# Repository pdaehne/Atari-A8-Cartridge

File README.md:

# Atari A8 Cartridge

This repository contains the KiCad project and Gerber files for a simple
cartridge for the Atari 8-Bit Computers (Atari 400/800/XL/XE/XEGS). It supports
8 KiB and 16 KiB cartridge images that do not need memory mappers. You may put
multiple cartridge images on one cartridge, and select which one of the images
to start by using DIP switches, pin headers and jumpers.

## Ordering the PCB

The subdirectory "gerber-files" contains a Zip file you can use to order the PCB
from PCB manufacturers like PCBWay or JLCPCB. Simply upload the Zip on their web
page. Order the standard PCB thickness of 1.6mm. I also recommend to order a
surface finish of ENIG with gold fingers and chamfered edges, because it is much
more durable than the default HASL finish.

## Building the Cartridge

### Bill of Materials

* __1x 27(C)512 / 27(C)256 / 27(C)128 / 27(C)64 EPROM__.

  This is where you store your cartridge images. 27(C)512 have a capacity of 64
  KiB, 27(C)256 have 32 KiB, 27(C)128 have 16 KiB, and 27(C)64 have 8 KiB.

* (Optional) __1x 28 Pin Socket 2.54mm pitch 15.42mm width__.

  This is the socket for the EPROM. It is optional, you can also solder the
  EPROM directly to the PCB, but I prefer to use sockets. Keep in mind that the
  cartridge will not fit into a cartridge shell when you use sockets.

* __1x Ceramic Capacitor 100nF 2.5mm pitch__.

  This is the blocking capacitor for the EPROM.

* (Optional) __4x 10 kOhm Resistors DIN 0207__.

  These are pull-up resistors. Three of them are used on the DIP switches for
  the address lines A13, A14 and A15. When you do not plan to use the DIP
  switches, you can leave them away. The last one of the resistors is used to
  create the Chip Select (<span style="text-decoration:overline">CS</span>)
  signal for the EPROM when using 16 KiB ROMs. When you do not plan to use 16
  KiB ROMs, you can leave that resistor away.

* (Optional) __2x Diodes 1N4148 DO-35__.

  These are switching diodes used to create the Chip Select
  (<span style="text-decoration:overline">CS</span>) signal for the EPROM when
  using 16 KiB ROMs. When you do not plan to use 16 KiB ROMs, you can leave
  these diodes away.

* (Optional) __1x 1x3 Pin Header 2.54mm pitch__.

  Used to switch between 8 KiB and 16 KiB ROMs. When you do not need to switch
  between 8 KiB and 16 KiB ROMs, you can leave this pin header away and select
  a static configuration with a solder jumper.

* (Optional) __1x 2x3 Pin Header 2.54mm pitch__.

  Used to select the signal that goes to the Chip Select
  (<span style="text-decoration:overline">CS</span>) pin of the EPROM. This pin
  header is optional, you can select a static configuration with a solder
  jumper.

* (Optional) __2x Jumpers 2.54mm pitch__.

  Used on the pin headers to select the signal that goes to the Chip Select
  (<span style="text-decoration:overline">CS</span>) pin of the EPROM as well
  as to switch between 8 KiB and 16 KiB ROMs.

### Soldering the Pull-up Resistors on the Address Lines

We start with soldering the three pull-up resistors on the DIP switches that
control the address lines A13, A14 and A15. These are optional - when you do not
plan to use the DIP switches, you can leave these three resistors away.

### Soldering the Pull-up Resistor and Diodes for the 16 KiB Chip Select Signal

Then, we solder the single pull-up resistor and the two diodes that generate the
Chip Select (<span style="text-decoration:overline">CS</span>) signal for 16 KiB
ROMs. These are also optional - when you do not plan to use 16 KiB ROMs, you can
leave the resistor and the diodes away.

### Soldering the EPROM Socket

Now we solder the EPROM socket. This socket is optional, you can also solder the
EPROM directly to the cartridge, but I prefer sockets. Keep in mind that the
EPROM in a socket does not fit any cartridge case!

When soldering the EPROM directly to the cartridge, of course you have to fill
it with data before doing so!

Make sure that the notch of the socket points into the direction marked on the
silk screen of the PCB (up in the image below).

### Soldering the Capacitor

Next, solder the blocking capacitor to the cartridge.

### Soldering the Pin Header for the Chip Select Signal

Next, we solder the pin header used to configure the Chip Select
(<span style="text-decoration:overline">CS</span>) signal. More in detail
information about the configuration of the cartridge using these pin headers is
available in the section [Using the Cartridge](#using-the-cartridge) below.

Using the pin headers is optional, you can also generate a static configuration
by using corresponding solder jumpers on the back of the cartridge. Keep in mind
that you will not be able to put the cartridge into a case when you use the pin
headers!

### Soldering the DIP Switch

Now, we solder the DIP switch used to configure the RD4 and RD5 signals of the
cartridge as well as the address lines A13, A14 and A15 of the EPROM. You should
orient the DIP switch so that the "on" position of the sliders is to the right
of the cartridge as shown in the image below.

Using the DIP switch is optional, you can also generate a static configuration
by using corresponding solder jumpers on the back of the cartridge. Keep in mind
that you will not be able to put the cartridge into a case when you use the DIP
switch.

### Soldering the Pin Header for Selecting 8 KiB or 16 KiB Cartridge ROMs 

Next, we solder the pin header used to configure the cartridge for 8 KiB or 16
KiB ROMs.

Using the pin headers is optional, you can also generate a static configuration
by using corresponding solder jumpers on the back of the cartridge. Keep in mind
that you will not be able to put the cartridge into a case when you use the pin
headers!

### 3D-Printing a Case

In the subdirectory "[case](case)" of this repository there are STL files you can use to
print a case for the cartridge on your 3D printer. I even managed to fit an
EPROM with its socket into this case, but your mileage may vary, depending on
the length of the EPROM legs. You need two self-tapping flat-headed M3 Phillips
screws. Mine had a length of 12mm, but any length between 10mm and 17mm should
work.

There are two variants of the top part of the case, one with holes you can use
to access the DIP switches and the pin headers, and one closed version in case
your cartridge uses a fixed configuration.

### Using the Cartridge

This section explains how to use the cartridge, i.e. how to burn one or more
cartridge images onto the EPROM, and how to configure the cartridge to start one
of the images. There are DIP switches and two pin headers on the cartridge for
configuration. Two of the DIP switches configure the RD4 and RD5 signal lines of
the cartridge, i.e. they tell the computer where in the address space the
cartridge should show up. The remaining DIP switches configure the address lines
A13, A14, and A15, i.e. they determine the location of the ROM file on the
EPROM. One of the pin headers configures the Chip Select
(<span style="text-decoration:overline">CS</span>) signal of the EPROM, and the
other pin header configures the cartridge for 8 KiB or 16 KiB ROMs. When you do
not need the flexibility of configuring the cartridge using DIP switches or pin
headers and jumpers, there are corresponding solder jumpers on the back of the
cartridge that you can use to create a fixed configuration using solder blobs.

You do not need to worry if your configuration is correct, neither the cartridge
nor you Atari computer can be damaged by a wrong configuration, it simply will
not work.

> [!WARNING]
> Never change the configuration while the Atari computer is running. Always
> switch off the computer before changing the configuration or plugging in or
> removing the cartridge from the computer, otherwise you may damage the
> cartridge or your computer.

There are three types of ROMs supported by this cartridge:

  1. 8 KiB ROMs that get mapped at address range 32768-40959 ($8000-$9fff). This
     type of ROM is almost never used.
  2. 8 KiB ROMs that get mapped at address range 40960-49151 ($a000-$bfff).
  3. 16 KiB ROMs that get mapped at address range 32768-49151 ($8000-$bfff).

The following table show the settings used to configure the cartridge for these
three types of ROMs (and a fourth configuration which disables the cartridge).
You have to set the RD4 and RD5 DIP switches, connect the top, middle or bottom
two pins of the 2x3 pin header for the Chip Select signal, and you have to
connect either the left two or the right two pins of the 3x1 pin header for the
8 KiB / 16 KiB ROM size:

| RD4 / RD5 | Chip Select | ROM Size | Meaning |
|-----------|-------------|----------| --------|
| <picture><source media="(prefers-color-scheme: dark)" srcset="images/rd4_off_rd5_off.dark.svg"></picture> | Does not matter | Does not matter | Cartridge is disabled |
| <picture><source media="(prefers-color-scheme: dark)" srcset="images/rd4_on_rd5_off.dark.svg"></picture> | <picture><source media="(prefers-color-scheme: dark)" srcset="images/CS_S4.dark.svg"></picture> | <picture><source media="(prefers-color-scheme: dark)" srcset="images/8k.dark.svg"></picture> | 8 KiB cartridge at address range 32768-40959 ($8000-$9fff) |
| <picture><source media="(prefers-color-scheme: dark)" srcset="images/rd4_off_rd5_on.dark.svg"></picture> | <picture><source media="(prefers-color-scheme: dark)" srcset="images/CS_S5.dark.svg"></picture> | <picture><source media="(prefers-color-scheme: dark)" srcset="images/8k.dark.svg"></picture> | 8 KiB cartridge at address range 40960-49151 ($a000-$bfff) |
| <picture><source media="(prefers-color-scheme: dark)" srcset="images/rd4_on_rd5_on.dark.svg"></picture> | <picture><source media="(prefers-color-scheme: dark)" srcset="images/CS_S4_S5.dark.svg"></picture> | <picture><source media="(prefers-color-scheme: dark)" srcset="images/16k.dark.svg"></picture> | 16 KiB cartridge at address range 32768-49151 ($8000-$bfff) |

All other configurations not shown in the above table are invalid!

The remaining three DIP switches for the address lines A13, A14 and A15
determine the location of the ROM on the EPROM. Moving a DIP switch to the right
sets the corresponding address line to logic "0", and moving the switch to the
left sets the address line to "1". The cartridge supports 27(C)512, 27(C)256,
27(C)128, and 27(C)64 EPROMs which have different capacities and can store
different numbers of ROMs.

On 27(C)512 EPROMs with 64 KiB capacity, there are 8 slots where you may put ROM
images. 8 KiB ROMs require one single slot and may start at any of these slots,
16 KiB ROMs require two slots and must start at slots 1, 3, 5 or 7. You can
arbitrarily mix different image sizes to fill the available space. The following
table shows all possible combinations:

| Address Lines | Meaning |
|---------------|---------|
| <picture><source media="(prefers-color-scheme: dark)" srcset="images/slot1.dark.svg"></picture> | Slot 1 at address range 0-8191 ($0-$1fff) |
| <picture><source media="(prefers-color-scheme: dark)" srcset="images/slot2.dark.svg"></picture> | Slot 2 at address range 8192-16383 ($2000-$3fff) |
| <picture><source media="(prefers-color-scheme: dark)" srcset="images/slot3.dark.svg"></picture> | Slot 3 at address range 16384-24575 ($4000-$5fff) |
| <picture><source media="(prefers-color-scheme: dark)" srcset="images/slot4.dark.svg"></picture> | Slot 4 at address range 24576-32767 ($6000-$7fff) |
| <picture><source media="(prefers-color-scheme: dark)" srcset="images/slot5.dark.svg"></picture> | Slot 5 at address range 32768-40959 ($8000-$9fff) |
| <picture><source media="(prefers-color-scheme: dark)" srcset="images/slot6.dark.svg"></picture> | Slot 6 at address range 40960-49151 ($a000-$bfff) |
| <picture><source media="(prefers-color-scheme: dark)" srcset="images/slot7.dark.svg"></picture> | Slot 7 at address range 49152-57343 ($c000-$dfff) |
| <picture><source media="(prefers-color-scheme: dark)" srcset="images/slot8.dark.svg"></picture> | Slot 8 at address range 57344-65535 ($e000-$ffff) |

On 27(C)256 EPROMs with 32 KiB capacity, there are 4 slots where you may put ROM
images. 8 KiB ROMs require one single slot and may start at any of these slots,
16 KiB ROMs require two slots and must start at slots 1 or 3. You can
arbitrarily mix different image sizes to fill the available space. A15 must
always be set to logical "1" on these EPROMs. The following table shows all
possible combinations:

| Address Lines | Meaning |
|---------------|---------|
| <picture><source media="(prefers-color-scheme: dark)" srcset="images/slot5.dark.svg"></picture> | Slot 1 at address range 0-8191 ($0-$1fff) |
| <picture><source media="(prefers-color-scheme: dark)" srcset="images/slot6.dark.svg"></picture> | Slot 2 at address range 8192-16383 ($2000-$3fff) |
| <picture><source media="(prefers-color-scheme: dark)" srcset="images/slot7.dark.svg"></picture> | Slot 3 at address range 16384-24575 ($4000-$5fff) |
| <picture><source media="(prefers-color-scheme: dark)" srcset="images/slot8.dark.svg"></picture> | Slot 4 at address range 24576-32767 ($6000-$7fff) |

On 27(C)128 EPROMs with 16 KiB capacity, there are 2 slots where you may put ROM
images. 8 KiB ROMs require one single slot and may start at any of these slots,
16 KiB ROMs require two slots and must start at slot 1. A14 and A15 must always
be set to logical "1" on these EPROMs. The following table shows all possible
combinations:

| Address Lines | Meaning |
|---------------|---------|
| <picture><source media="(prefers-color-scheme: dark)" srcset="images/slot7.dark.svg"></picture> | Slot 1 at address range 0-8191 ($0-$1fff) |
| <picture><source media="(prefers-color-scheme: dark)" srcset="images/slot8.dark.svg"></picture> | Slot 2 at address range 8192-16383 ($2000-$3fff) |

On 27(C)64 EPROMs with 8 KiB capacity, there is one single slot where you may put
one single 8 KiB ROM. A13, A14 and A15 must always be set to logical "1" on
these EPROMs. The following table shows the only possible combination:

| Address Lines | Meaning |
|---------------|---------|
| <picture><source media="(prefers-color-scheme: dark)" srcset="images/slot8.dark.svg"></picture> | Slot 1 at address range 0-8191 ($0-$1fff) |

#### Example

In this section I will demonstrate how to burn two 8 KiB cartridge images and
two 16 KiB cartridge images onto a 27(C)512 EPROM using the popular TL866
programmer and its Xgpro software. I selected the following images:

* The "Atari 65/130 XE Rev. 3.4 Test Cartridge", a 8 KiB ROM that I put into
  slot 1 of the cartridge.
* The game "Galaxian", a 8 KiB ROM that I put into slot 2 of the cartridge.
* The game "Donkey Kong", a 16 KiB ROM that I put into slots 3 and 4 of the
  cartridge.
* The game "Pac Man", a 16 KiB ROM that I put into slots 5 and 6 of the
  cartridge.

The last 16 KiB of the EPROM will stay empty for now.

In the software of my programmer we select the correct EPROM (a Winbond
W27C512 in my case). First, we have to program the 8 KiB image for the Atari
Test Cartridge. In the file selection dialog, we select the cartridge file
("65-130XE_Diagnostic_Cartridge_3.4.car"). This is a "car" file that has an
additional header of 16 bytes in front of the actual ROM image that we have to
remove. In the "Load mode" box, we set the "From File Start Addr(Hex)" to
"00010", which is the hexadecimal notation of decimal 16, and the "TO Buffer
Strat Addr(HEX)" (there actually is a typo in the software ) to "00000". So we
load the image without the 16 byte header to the first slot of the EPROM.

Now, we have to load the 8 KiB image of Galaxian into the second slot of the
EPROM. In the file selection dialog, we select the image file "Galaxian
(1982)(Atari)(US).bin". This is the raw image data without any header. In the
"Load mode" box, we set the "From File Start Addr(Hex)" to "00000", and the "TO
Buffer Strat Addr(HEX)" to "02000", which is the hexadecimal notation of decimal
8192. Now, we have to switch the "Clear Buffer when loading the file" selection
box to "disable", otherwise we will loose the data we loaded in the previous
step.

Next, we have to load the 16 KiB image of Donkey Kong into the third and fourth
slots of the EPROM. In the file selection dialog, we select the image file
"Donkey Kong.rom". This also is a raw image without a header. In the "Load
mode" box, we set the "From File Start Addr(Hex)" to "00000", and the "TO Buffer
Strat Addr(HEX)" to "04000", which is the hexadecimal notation of decimal 16384.
Again, we have to switch the "Clear Buffer when loading the file" selection box
to "disable" to prevent clearing the data from the previous steps.

Last, we have to load the 16 KiB image of Pac Man into the fifth and sixth
slots of the EPROM. In the file selection dialog, we select the image file
"pacman.rom". Again this is a raw image without a header. In the "Load mode"
box, we set the "From File Start Addr(Hex)" to "00000", and the "TO Buffer Strat
Addr(HEX)" to "08000", which is the hexadecimal notation of decimal 32768.
We have to switch the "Clear Buffer when loading the file" selection box to
"disable" to prevent clearing the data from the previous steps.

Now we are finished with loading the image files. We burn the data to the EPROM
and put the EPROM onto the cartridge with the notch of the EPROM pointing into
the direction marked onto the silk screen. The following table shows the
settings we need to make to use the ROM images:

| RD4 / RD5 | Chip Select | ROM Size | Address Lines | ROM Image |
|-----------|-------------|----------| --------------|-----------|
| <picture><source media="(prefers-color-scheme: dark)" srcset="images/rd4_off_rd5_on.dark.svg"></picture> | <picture><source media="(prefers-color-scheme: dark)" srcset="images/CS_S5.dark.svg"></picture> | <picture><source media="(prefers-color-scheme: dark)" srcset="images/8k.dark.svg"></picture> | <picture><source media="(prefers-color-scheme: dark)" srcset="images/slot1.dark.svg"></picture> | 65/130 XE Test |
| <picture><source media="(prefers-color-scheme: dark)" srcset="images/rd4_off_rd5_on.dark.svg"></picture> | <picture><source media="(prefers-color-scheme: dark)" srcset="images/CS_S5.dark.svg"></picture> | <picture><source media="(prefers-color-scheme: dark)" srcset="images/8k.dark.svg"></picture> | <picture><source media="(prefers-color-scheme: dark)" srcset="images/slot2.dark.svg"></picture> | Galaxian |
| <picture><source media="(prefers-color-scheme: dark)" srcset="images/rd4_on_rd5_on.dark.svg"></picture> | <picture><source media="(prefers-color-scheme: dark)" srcset="images/CS_S4_S5.dark.svg"></picture> | <picture><source media="(prefers-color-scheme: dark)" srcset="images/16k.dark.svg"></picture> | <picture><source media="(prefers-color-scheme: dark)" srcset="images/slot3.dark.svg"></picture> | Donkey Kong |
| <picture><source media="(prefers-color-scheme: dark)" srcset="images/rd4_on_rd5_on.dark.svg"></picture> | <picture><source media="(prefers-color-scheme: dark)" srcset="images/CS_S4_S5.dark.svg"></picture> | <picture><source media="(prefers-color-scheme: dark)" srcset="images/16k.dark.svg"></picture> | <picture><source media="(prefers-color-scheme: dark)" srcset="images/slot5.dark.svg"></picture> | Pac Man |

#### Putting the Cartridge into an Atari 8-Bit Machine

> [!WARNING]
> Before sticking the cartridge into your Atari, make sure the computer is
> switched off, otherwise you might damage either the computer or the cartridge!

Set the right configuration of the RD4/RD5 signals, the Chip Select
(<span style="text-decoration:overline">CS</span>) signal, the ROM size (8 or 16
KiB), and the A13, A14 and A15 address lines of the EPROM for the image you want
to start using the DIP switches, pin headers and jumpers. Carefully stick the
cartridge into the cartridge slot of your Atari 8-Bit machine. When you do not
use a cartridge case, you have to be careful not to damage the cartridge port or
any flaps on the port. Also make sure that you insert the cartridge in the right
orientation - on the XL, the side of the cartridge with the EPROM has to face to
the back, and on the XE, the EPROM has to face to the bottom!

## License

Atari A8 Cartridge (c) by Patrick Dähne

Atari A8 Cartridge is licensed under a
Creative Commons Attribution-NonCommercial-ShareAlike 4.0 International License.

You should have received a copy of the license along with this
work. If not, see <https://creativecommons.org/licenses/by-nc-sa/4.0/>.

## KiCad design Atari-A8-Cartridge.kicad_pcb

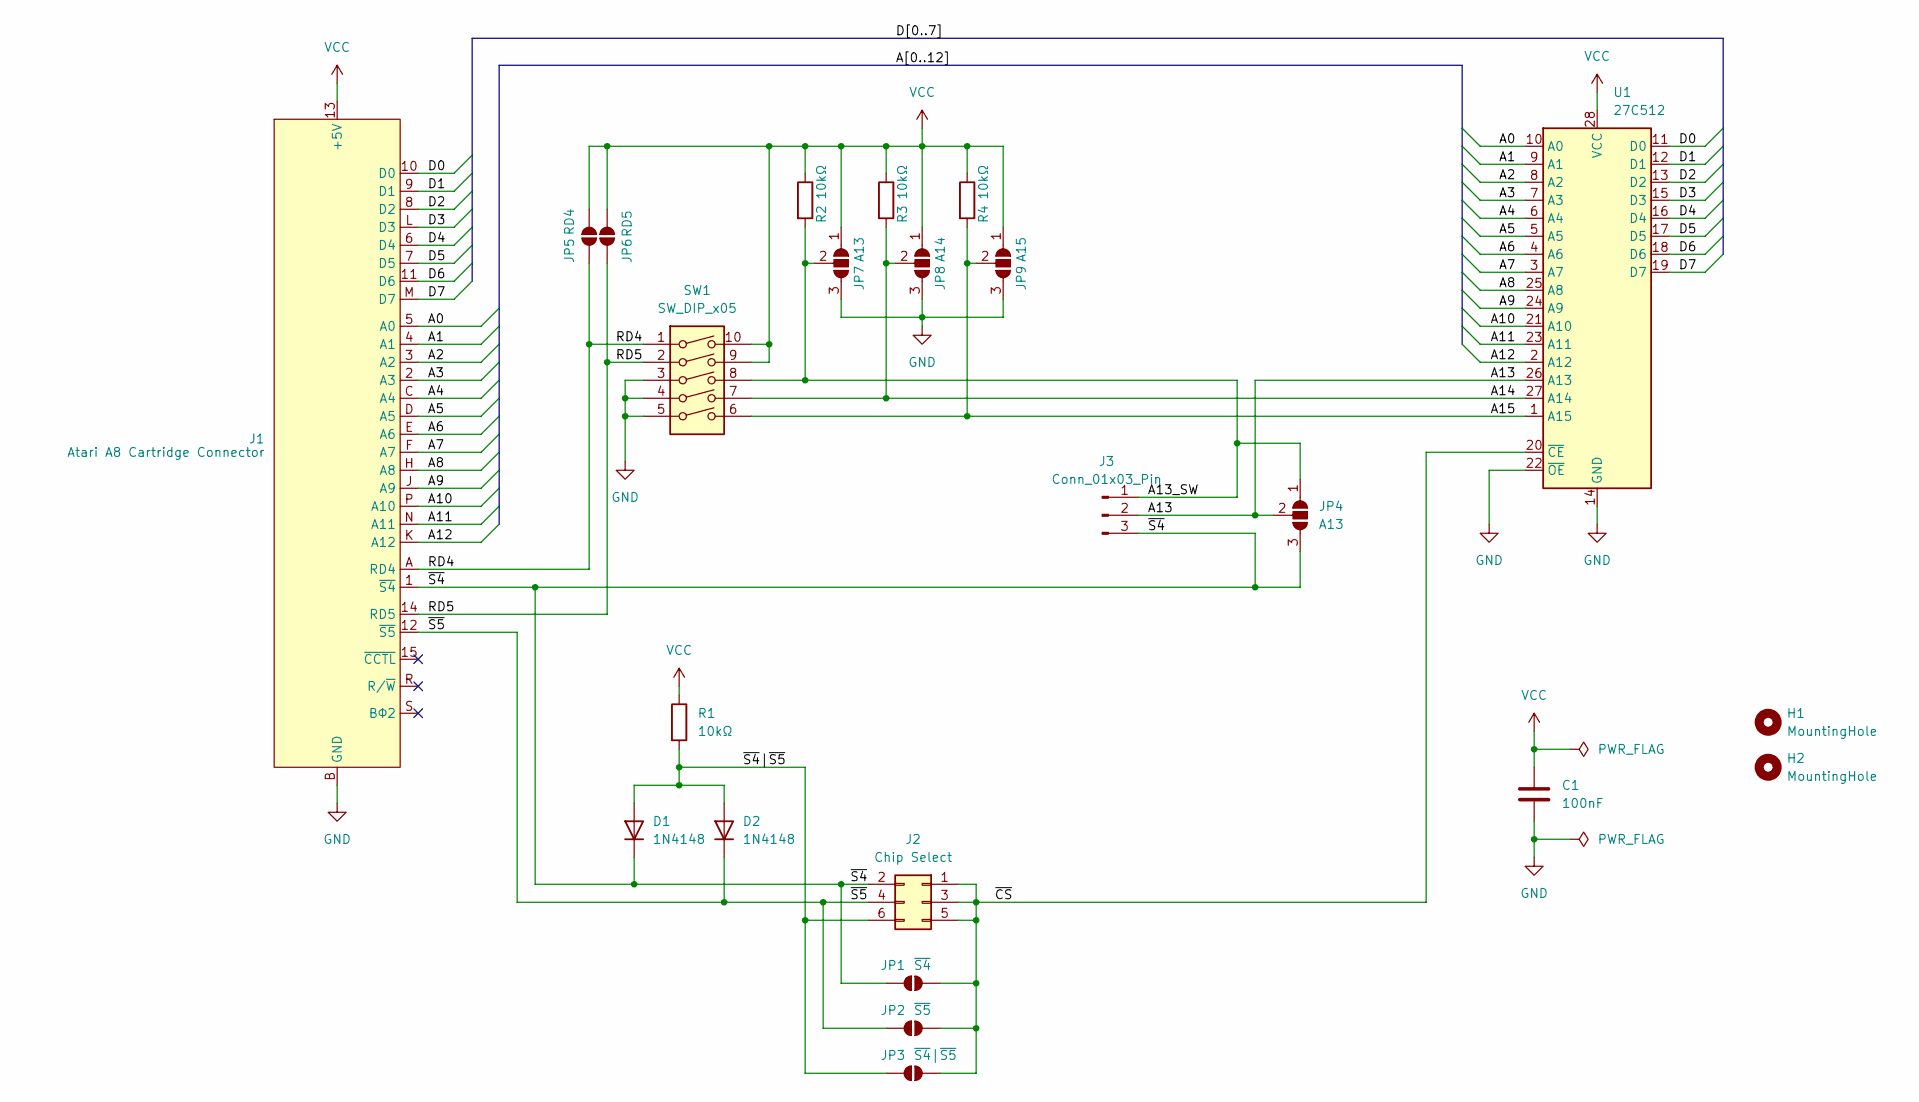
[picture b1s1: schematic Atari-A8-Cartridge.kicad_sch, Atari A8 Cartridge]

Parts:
C1: 100nF; C_Disc_D3.0mm_W1.6mm_P2.50mm
D1, D2: 1N4148; D_DO-35_SOD27_P7.62mm_Horizontal
H1, H2: MountingHole; MountingHole_6mm
J1: Atari A8 Cartridge Connector; Cartridge
J2: Chip Select; PinHeader_2x03_P2.54mm_Vertical
J3: Conn_01x03_Pin; PinHeader_1x03_P2.54mm_Vertical
JP1: ~{S4}; SolderJumper-2_P1.3mm_Open_RoundedPad1.0x1.5mm
JP2: ~{S5}; SolderJumper-2_P1.3mm_Open_RoundedPad1.0x1.5mm
JP3: ~{S4}|~{S5}; SolderJumper-2_P1.3mm_Open_RoundedPad1.0x1.5mm
JP4, JP7: A13; SolderJumper-3_P1.3mm_Open_RoundedPad1.0x1.5mm
JP5: RD4; SolderJumper-2_P1.3mm_Open_RoundedPad1.0x1.5mm
JP6: RD5; SolderJumper-2_P1.3mm_Open_RoundedPad1.0x1.5mm
JP8: A14; SolderJumper-3_P1.3mm_Open_RoundedPad1.0x1.5mm
JP9: A15; SolderJumper-3_P1.3mm_Open_RoundedPad1.0x1.5mm
R1, R2, R3, R4: 10kΩ; R_Axial_DIN0207_L6.3mm_D2.5mm_P10.16mm_Horizontal
SW1: SW_DIP_x05; SW_DIP_SPSTx05_Slide_9.78x14.88mm_W7.62mm_P2.54mm
U1: 27C512; DIP-28_W15.24mm_Socket_LongPads

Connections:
/A0: J1.5 (A0), U1.10 (A0)
/A1: J1.4 (A1), U1.9 (A1)
/A2: J1.3 (A2), U1.8 (A2)
/A3: J1.2 (A3), U1.7 (A3)
/A4: J1.C (A4), U1.6 (A4)
/A5: J1.D (A5), U1.5 (A5)
/A6: J1.E (A6), U1.4 (A6)
/A7: J1.F (A7), U1.3 (A7)
/A8: J1.H (A8), U1.25 (A8)
/A9: J1.J (A9), U1.24 (A9)
/A10: J1.P (A10), U1.21 (A10)
/A11: J1.N (A11), U1.23 (A11)
/A12: J1.K (A12), U1.2 (A12)
/A13: J3.2, JP4.2 (C), U1.26 (A13)
/A13_SW: J3.1, JP4.1 (A), JP7.2 (C), R2.2, SW1.8
/A14: JP8.2 (C), R3.2, SW1.7, U1.27 (A14)
/A15: JP9.2 (C), R4.2, SW1.6, U1.1 (A15)
/D0: J1.10 (D0), U1.11 (D0)
/D1: J1.9 (D1), U1.12 (D1)
/D2: J1.8 (D2), U1.13 (D2)
/D3: J1.L (D3), U1.15 (D3)
/D4: J1.6 (D4), U1.16 (D4)
/D5: J1.7 (D5), U1.17 (D5)
/D6: J1.11 (D6), U1.18 (D6)
/D7: J1.M (D7), U1.19 (D7)
/RD4: J1.A (RD4), JP5.2 (B), SW1.1
/RD5: J1.14 (RD5), JP6.2 (B), SW1.2
/~CS: J2.1, J2.3, J2.5, JP1.2 (B), JP2.2 (B), JP3.2 (B), U1.20 (~CE)
/~S4: D1.1 (K), J1.1 (~S4), J2.2, J3.3, JP1.1 (A), JP4.3 (B)
/~S4|~S5: D1.2 (A), D2.2 (A), J2.6, JP3.1 (A), R1.2
/~S5: D2.1 (K), J1.12 (~S5), J2.4, JP2.1 (A)
GND: C1.2, J1.B (GND), JP7.3 (B), JP8.3 (B), JP9.3 (B), SW1.3, SW1.4, SW1.5, U1.14 (GND), U1.22 (~OE)
VCC: C1.1, J1.13 (+5V), JP5.1 (A), JP6.1 (A), JP7.1 (A), JP8.1 (A), JP9.1 (A), R1.1, R2.1, R3.1, R4.1, SW1.9, SW1.10, U1.28 (VCC)

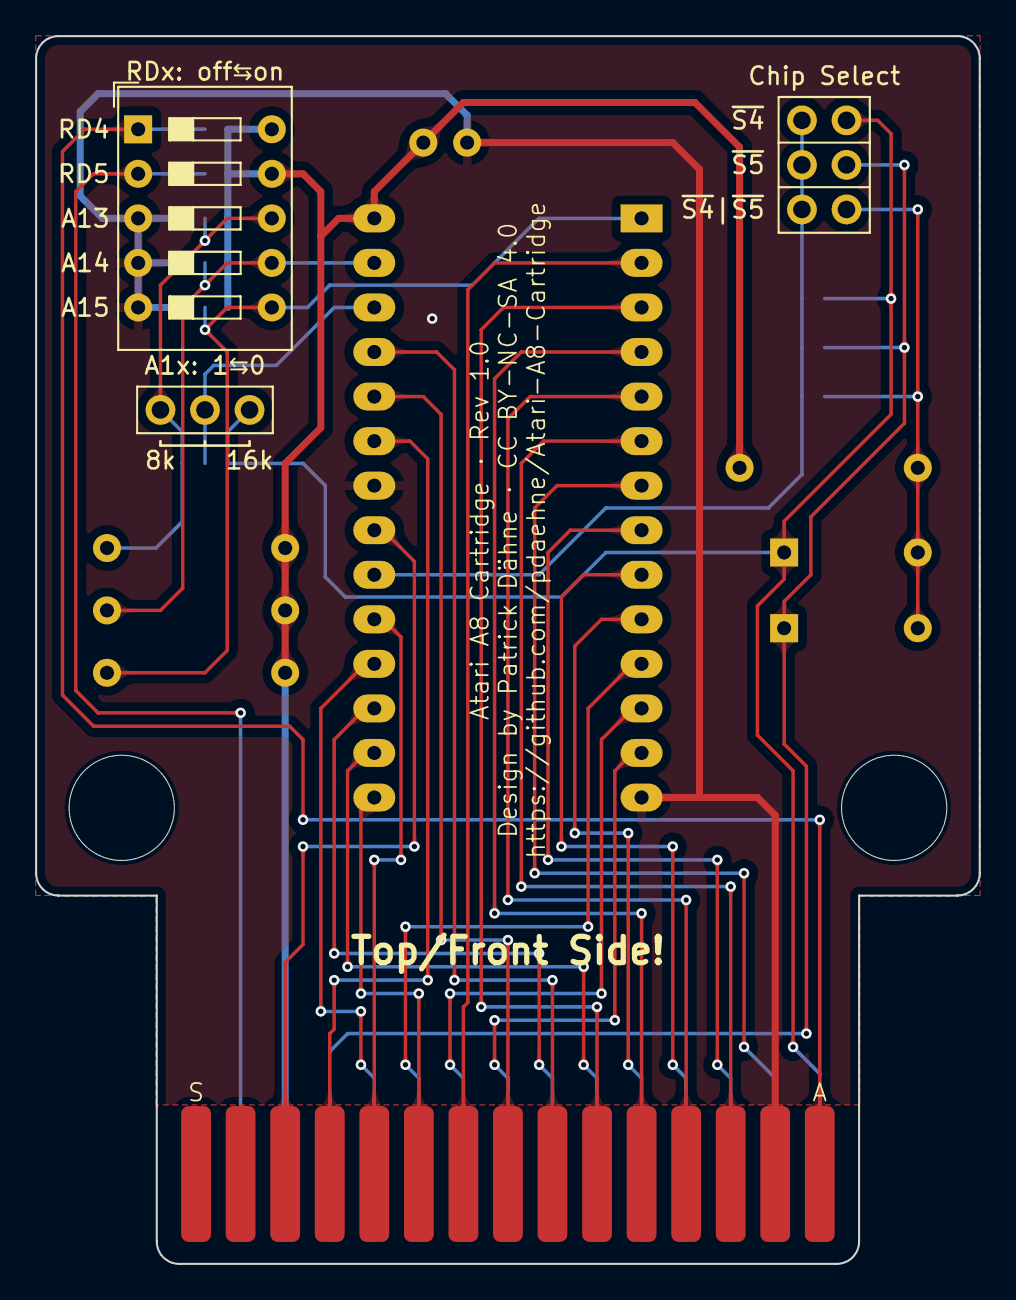
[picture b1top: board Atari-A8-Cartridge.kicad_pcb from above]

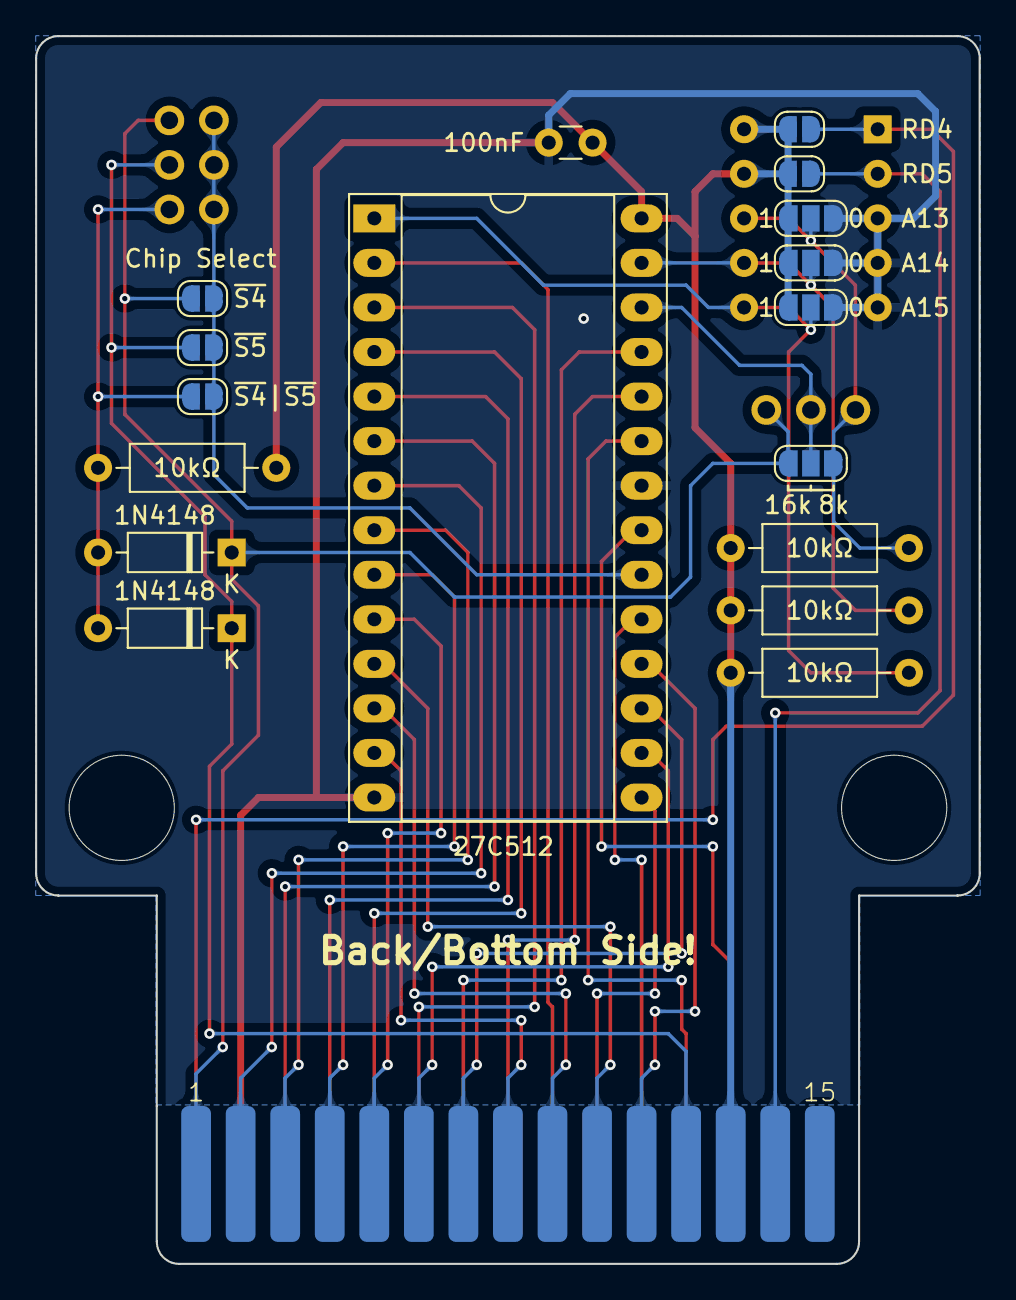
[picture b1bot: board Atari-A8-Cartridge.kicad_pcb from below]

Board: 2 copper layers, 53.8 x 70.0 mm, 23 parts (17 on the bottom side), 33 nets.

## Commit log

2025-11-03 Initial check-in
2025-11-26 Wrote README
2025-12-03 Fixed some typos
2026-05-06 Added case

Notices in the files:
README.md:
License:
Atari A8 Cartridge (c) by Patrick Dähne
Atari A8 Cartridge is licensed under a
Creative Commons Attribution-NonCommercial-ShareAlike 4.0 International License.
You should have received a copy of the license along with this
work. If not, see .
Atari-A8-Cartridge.kicad_pcb:
Patrick Dähne CC BY-NC-SA 4.0
Design by Patrick Dähne · CC BY-NC-SA 4.0
